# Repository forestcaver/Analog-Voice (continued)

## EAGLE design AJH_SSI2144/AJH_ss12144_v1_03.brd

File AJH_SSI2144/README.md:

# SSI 2144 LPF

Built and tested

CC-BY-NC-SA 4.0

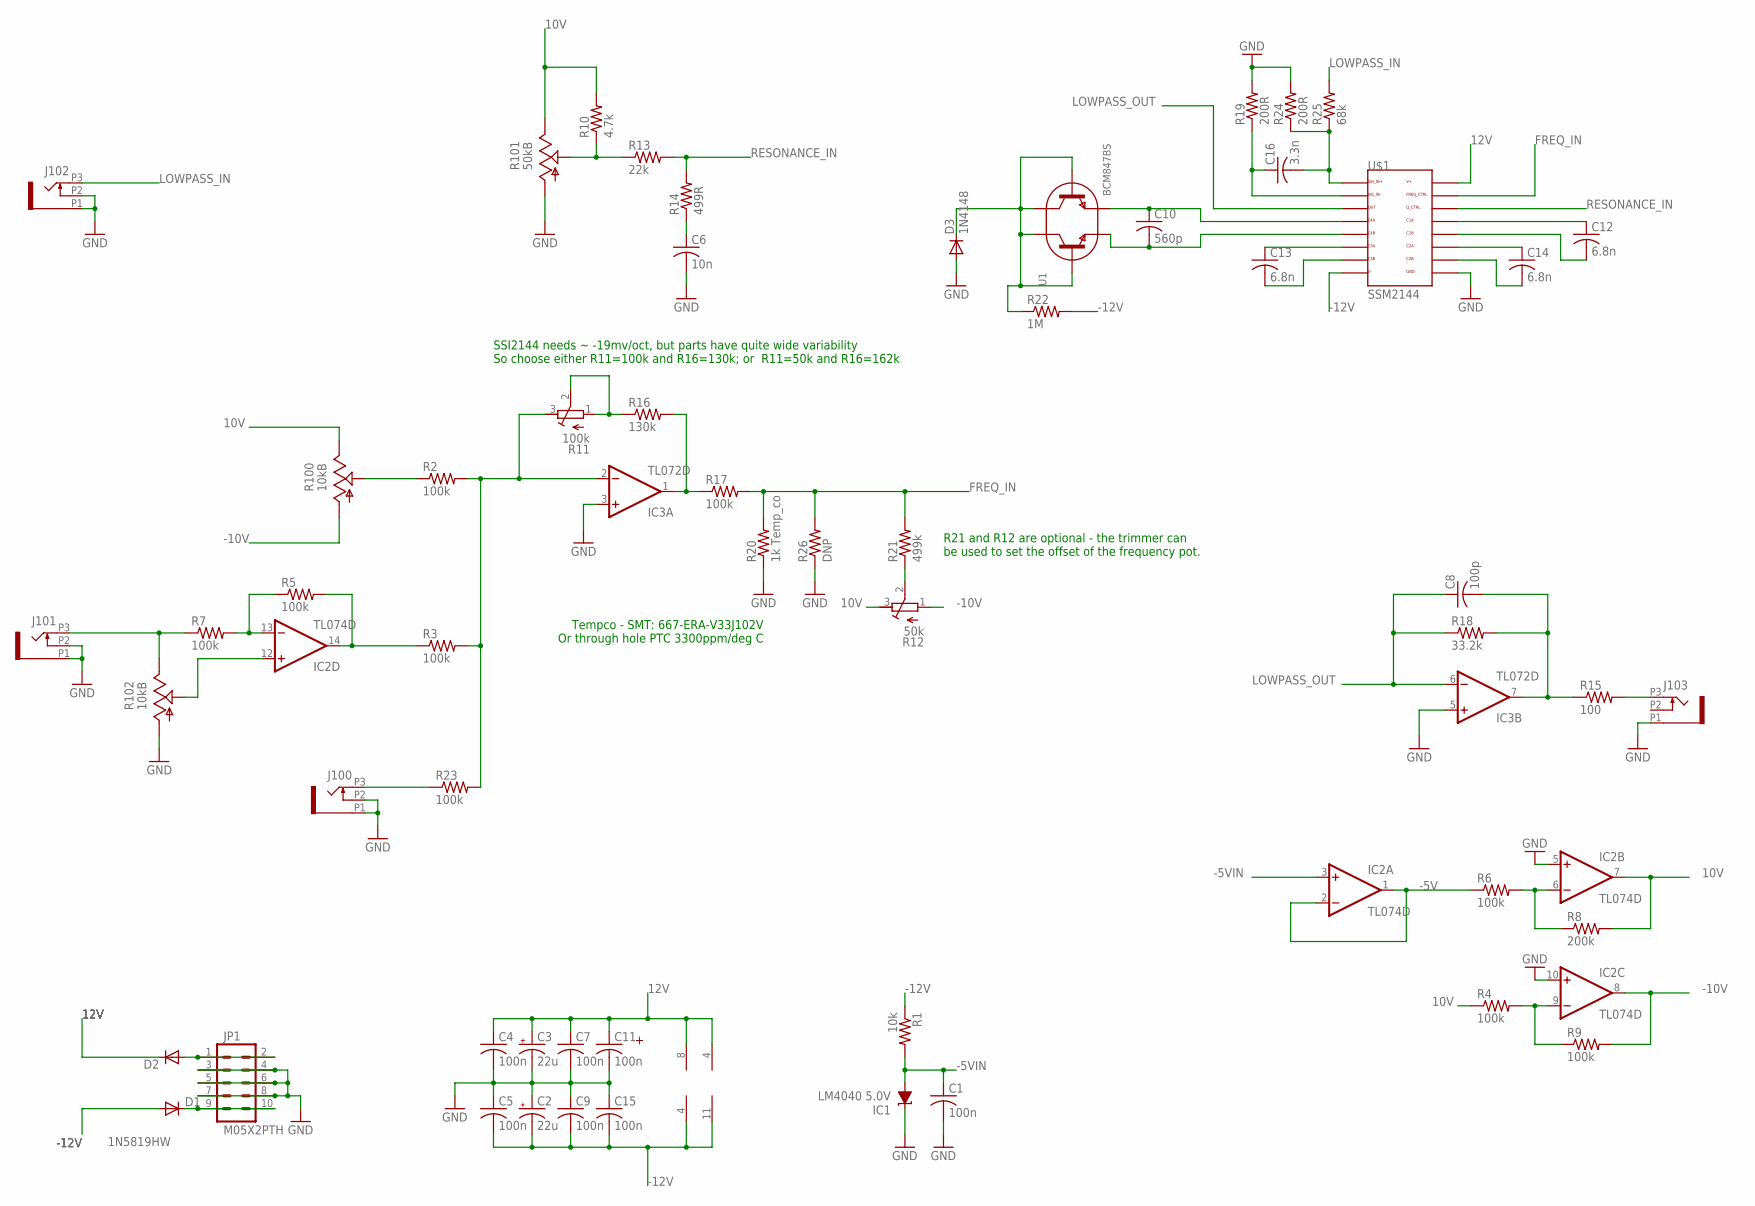
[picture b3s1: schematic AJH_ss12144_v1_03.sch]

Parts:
C1, C4, C5, C7, C9, C11, C15: 100n; C0603
C2, C3: 22u; PANASONIC_B
C6: 10n; C0603
C8: 100p; C0603
C10: 560p; C0603
C12, C13, C14: 6.8n; C0603
C16: 3.3n; C0603
D1, D2: 1N5819HW; SOD123
D3: 1N4148; SOD523
IC1: LM4040 5.0V; DBZ_R-PDSO-G3
IC2: TL074D; SO14
IC3: TL072D; SO08
J100, J101, J102, J103: PJ301_THONKICONN6; WQP_PJ_301M6
JP1: M05X2PTH; AVR_ICSP
R1: 10k; R0603
R2, R3, R4, R5, R6, R7, R9, R17, R23: 100k; R0603
R8: 200k; R0603
R10: 4.7k; R0603
R11: 100k; RTRIM3296X
R12: 50k; RTRIM3296X
R13: 22k; R0603
R14: 499R; R0603
R15: 100; R0603
R16: 130k; R0603
R18: 33.2k; R0603
R19, R24: 200R; R0603
R20: 1k Temp_co; R0603
R21: 499k; R0603
R22: 1M; R0603
R25: 68k; R0603
R26: DNP; 0204/7
R100, R102: 10kB; ALPS_POT_VERTICAL
R101: 50kB; ALPS_POT_VERTICAL
U1: BCM847BS; SOT363
U$1: SSM2144; SSOP16

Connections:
10V: IC2.7 (OUT), R4.1, R8.2, R10.2, R12.3 (A), R100.P$1 (E), R101.P$1 (E)
12V: C3.+, C4.1, C7.1, C11.1, D2.C, IC2.4 (V+), IC3.8 (V+), U$1.16 (V+)
-5V: IC2.1 (OUT), IC2.2 (-IN), R6.1
-5VIN: C1.1, IC1.2 (A), IC2.3 (+IN), R1.2
-10V: IC2.8 (OUT), R9.2, R12.1 (E), R100.P$3 (A)
-12V: C2.-, C5.2, C9.2, C15.2, D1.A, IC2.11 (V-), IC3.4 (V-), R1.1, R22.2, U$1.8 (V-)
FREQ_IN: R17.2, R20.2, R21.2, R26.2, U$1.15 (FREQ_CTRL)
GND: C1.2, C2.+, C3.-, C4.2, C5.1, C6.2, C7.2, C9.1, C11.2, C15.1, D3.A, IC1.1 (C), IC2.5 (+IN), IC2.10 (+IN), IC3.3 (+IN), IC3.5 (+IN), J100.P1 (1), J100.P2 (2), J101.P1 (1), J101.P2 (2), J102.P1 (1), J102.P2 (2), J103.P1 (1), JP1.3, JP1.4, JP1.5, JP1.6, JP1.7, JP1.8, R19.2, R20.1, R24.2, R26.1, R101.P$3 (A), R102.P$3 (A), U$1.9 (GND)
LOWPASS_IN: J102.P3 (3), R25.2
LOWPASS_OUT: C8.1, IC3.6 (-IN), R18.1, U$1.3 (OUT)
unnamed: C8.2, IC3.7 (OUT), R15.1, R18.2
unnamed: C13.1, U$1.6 (C3A)
unnamed: IC2.12 (+IN), R102.P$2 (S)
unnamed: R2.1, R100.P$2 (S)
unnamed: IC2.13 (-IN), R5.1, R7.2
unnamed: D2.A, JP1.1, JP1.2
unnamed: IC3.2 (-IN), R2.2, R3.2, R11.3 (A), R23.2
unnamed: IC3.1 (OUT), R16.2, R17.1
unnamed: C10.1, U1.4 (E2), U$1.4 (C4A)
unnamed: J100.P3 (3), R23.1
unnamed: J103.P3 (3), R15.2
unnamed: IC2.14 (OUT), R3.1, R5.2
unnamed: IC2.9 (-IN), R4.2, R9.1
unnamed: D3.C, R22.1, U1.2 (B1), U1.3 (C2), U1.5 (B2), U1.6 (C1)
unnamed: IC2.6 (-IN), R6.2, R8.1
unnamed: C10.2, U1.1 (E1), U$1.5 (C4B)
unnamed: C13.2, U$1.7 (C3B)
unnamed: C14.2, U$1.10 (C2B)
unnamed: C14.1, U$1.11 (C2A)
unnamed: D1.C, JP1.9, JP1.10
unnamed: C12.1, U$1.13 (C1A)
unnamed: C12.2, U$1.12 (C1B)
unnamed: C16.1, R19.1, U$1.2 (SIG_IN-)
unnamed: R10.1, R13.1, R101.P$2 (S)
unnamed: C6.1, R14.1
unnamed: R12.2 (S), R21.1
unnamed: C16.2, R24.1, R25.1, U$1.1 (SIG_IN+)
unnamed: R11.1 (E), R11.2 (S), R16.1
unnamed: J101.P3 (3), R7.1, R102.P$1 (E)
RESONANCE_IN: R13.2, R14.2, U$1.14 (Q_CTRL)

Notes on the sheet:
Tempco - SMT: 667-ERA-V33J102V Or through hole PTC 3300ppm/deg C
SSI2144 needs ~ -19mv/oct, but parts have quite wide variability So choose either R11=100k and R16=130k; or R11=50k and R16=162k
R21 and R12 are optional - the trimmer can be used to set the offset of the frequency pot.

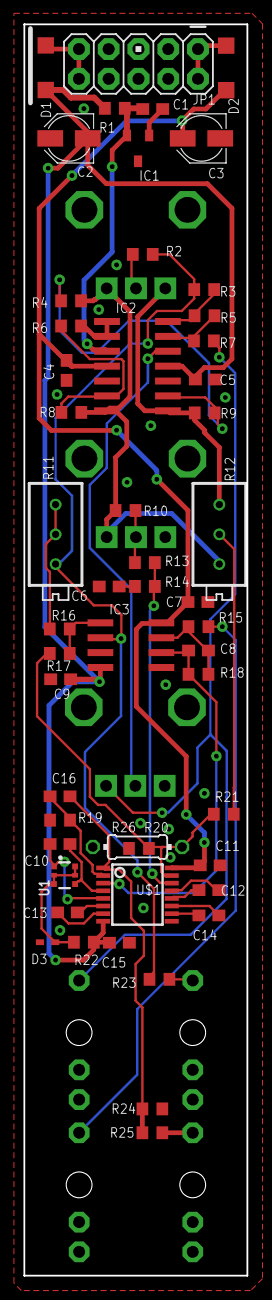
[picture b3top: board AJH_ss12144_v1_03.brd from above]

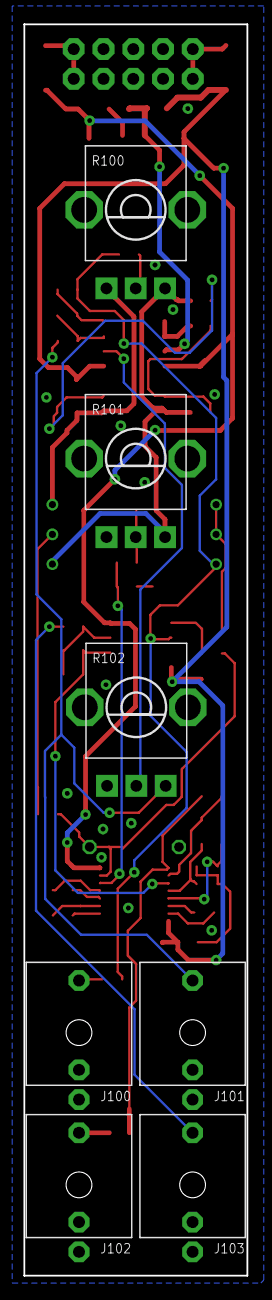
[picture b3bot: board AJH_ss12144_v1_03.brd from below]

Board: 2 copper layers, 19.0 x 106.8 mm, 58 parts (7 on the bottom side), 40 nets.

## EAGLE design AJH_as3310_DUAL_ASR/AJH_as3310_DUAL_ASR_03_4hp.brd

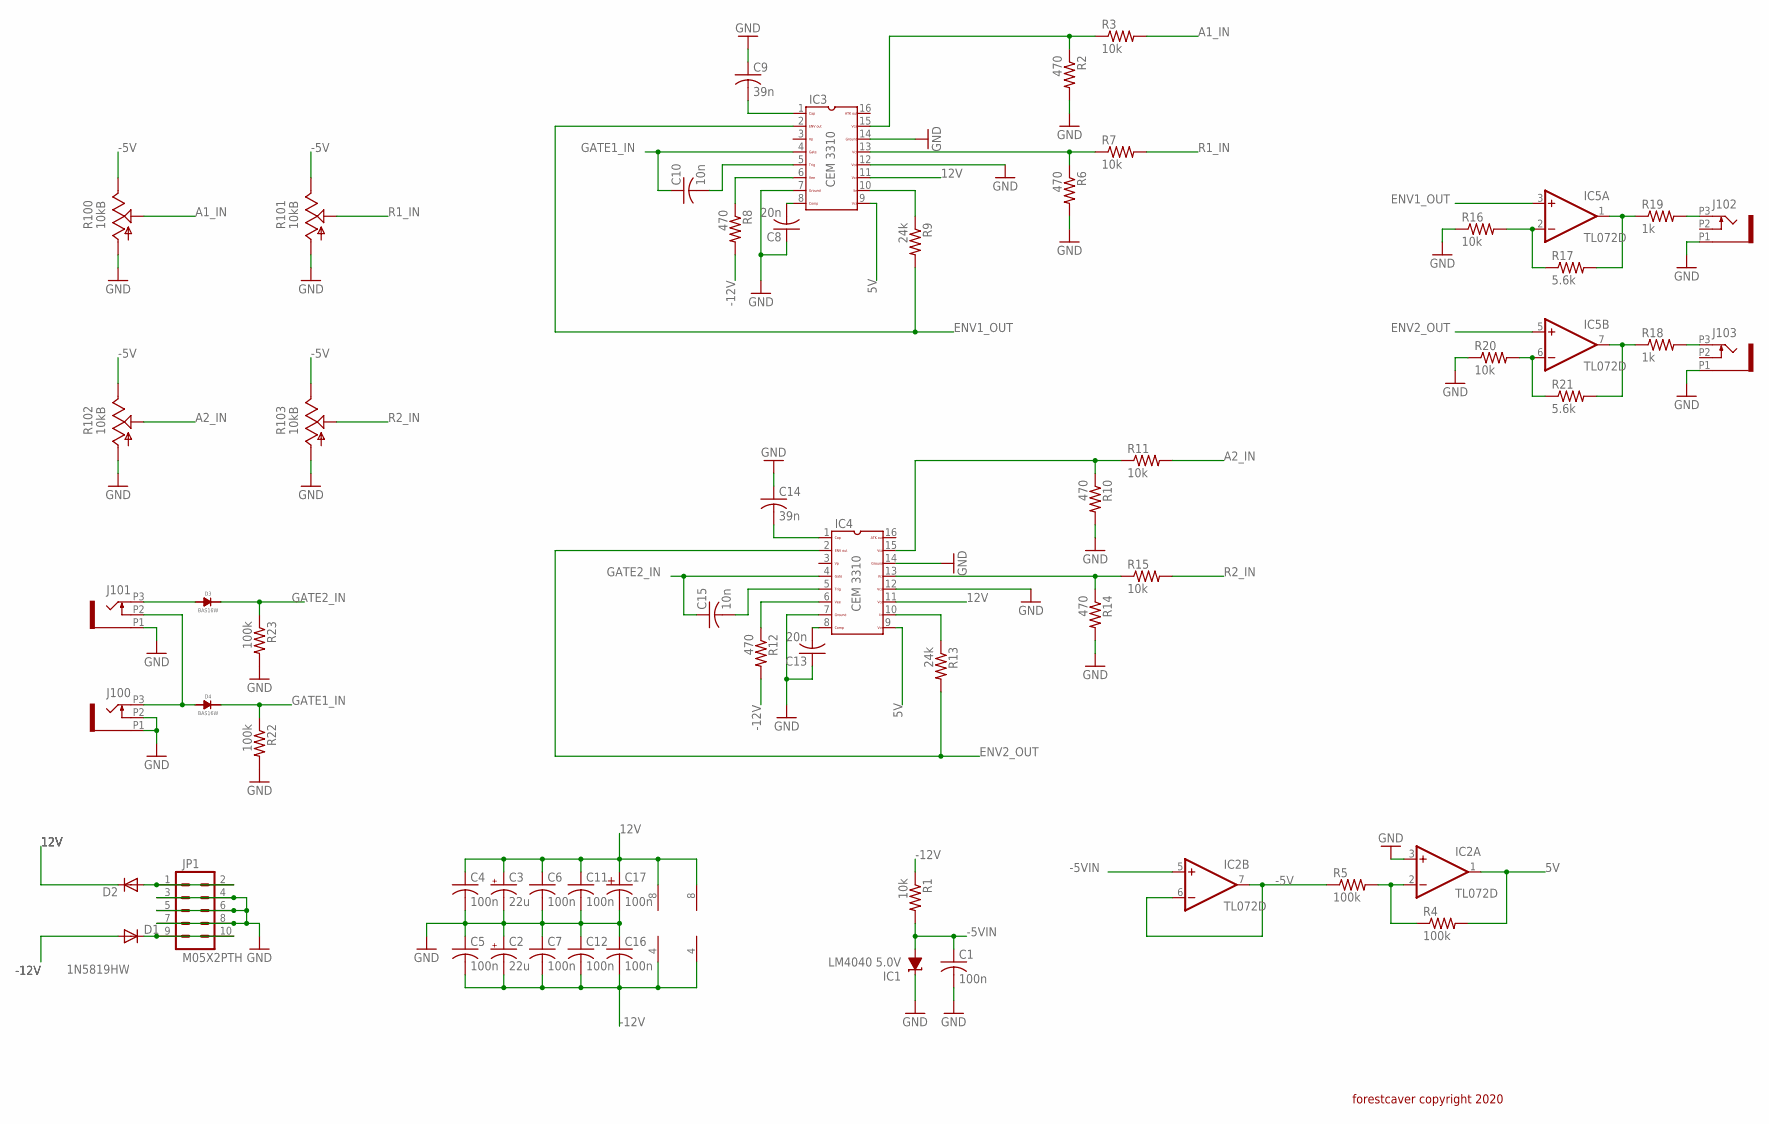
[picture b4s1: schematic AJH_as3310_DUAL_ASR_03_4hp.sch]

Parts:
C1, C4, C5, C6, C7, C11, C12, C16, C17: 100n; C0603
C2, C3: 22u; PANASONIC_B
C8, C13: 20n; C0603
C9, C14: 39n; C0603
C10, C15: 10n; C0603
D1, D2: 1N5819HW; SOD123
D3, D4: BAS16W; SOT-323
IC1: LM4040 5.0V; DBZ_R-PDSO-G3
IC2, IC5: TL072D; SO08
IC3, IC4: CEM3310SOIC16; SO16
J100, J101, J102, J103: PJ301_THONKICONN6; WQP_PJ_301M6
JP1: M05X2PTH; AVR_ICSP
R1, R3, R7, R11, R15, R16, R20: 10k; R0603
R2, R6, R8, R10, R12, R14: 470; R0603
R4, R5, R22, R23: 100k; R0603
R9, R13: 24k; R0603
R17, R21: 5.6k; R0603
R18, R19: 1k; R0603
R100, R101, R102, R103: 10kB; ALPS_POT_VERTICAL

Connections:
5V: IC2.1 (OUT), IC3.9, IC4.9, R4.2
12V: C3.+, C4.1, C6.1, C11.1, C17.1, D2.C, IC2.8 (V+), IC3.11, IC4.11, IC5.8 (V+)
-5V: IC2.6 (-IN), IC2.7 (OUT), R5.1, R100.P$1 (E), R101.P$1 (E), R102.P$1 (E), R103.P$1 (E)
-5VIN: C1.1, IC1.2 (A), IC2.5 (+IN), R1.2
-12V: C2.-, C5.2, C7.2, C12.2, C16.2, D1.A, IC2.4 (V-), IC5.4 (V-), R1.1, R8.2, R12.2
A1_IN: R3.2, R100.P$2 (S)
A2_IN: R11.2, R102.P$2 (S)
ENV1_OUT: IC3.2, IC5.3 (+IN), R9.2
ENV2_OUT: IC4.2, IC5.5 (+IN), R13.2
GATE1_IN: C10.1, D4.CATHODE, IC3.4, R22.1
GATE2_IN: C15.1, D3.CATHODE, IC4.4, R23.1
GND: C1.2, C2.+, C3.-, C4.2, C5.1, C6.2, C7.1, C8.1, C9.1, C11.2, C12.1, C13.1, C14.1, C16.1, C17.2, IC1.1 (C), IC2.3 (+IN), IC3.7, IC3.12, IC3.14, IC4.7, IC4.12, IC4.14, J100.P1 (1), J100.P2 (2), J101.P1 (1), J102.P1 (1), J103.P1 (1), JP1.3, JP1.4, JP1.5, JP1.6, JP1.7, JP1.8, R2.2, R6.2, R10.2, R14.2, R16.1, R20.1, R22.2, R23.2, R100.P$3 (A), R101.P$3 (A), R102.P$3 (A), R103.P$3 (A)
unnamed: D3.ANODE, J101.P3 (3)
unnamed: C15.2, IC4.5
unnamed: C9.2, IC3.1
unnamed: C8.2, IC3.8
unnamed: C10.2, IC3.5
unnamed: D2.A, JP1.1, JP1.2
unnamed: IC3.13, R6.1, R7.1
unnamed: IC3.6, R8.1
unnamed: C13.2, IC4.8
unnamed: IC3.10, R9.1
unnamed: IC4.6, R12.1
unnamed: IC3.15, R2.1, R3.1
unnamed: IC2.2 (-IN), R4.1, R5.2
unnamed: C14.2, IC4.1
unnamed: IC4.10, R13.1
unnamed: IC4.13, R14.1, R15.1
unnamed: IC4.15, R10.1, R11.1
unnamed: IC5.6 (-IN), R20.2, R21.1
unnamed: IC5.7 (OUT), R18.1, R21.2
unnamed: D1.C, JP1.9, JP1.10
unnamed: IC5.2 (-IN), R16.2, R17.1
unnamed: IC5.1 (OUT), R17.2, R19.1
unnamed: J102.P3 (3), R19.2
unnamed: J103.P3 (3), R18.2
unnamed: D4.ANODE, J100.P3 (3), J101.P2 (2)
R1_IN: R7.2, R101.P$2 (S)
R2_IN: R15.2, R103.P$2 (S)

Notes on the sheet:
forestcaver copyright 2020

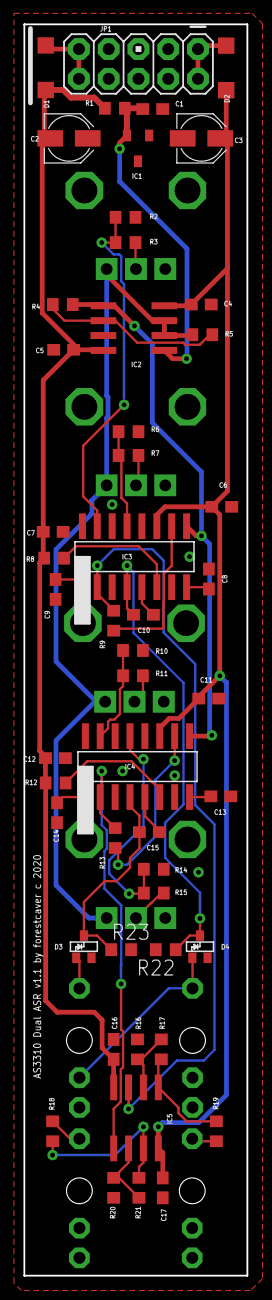
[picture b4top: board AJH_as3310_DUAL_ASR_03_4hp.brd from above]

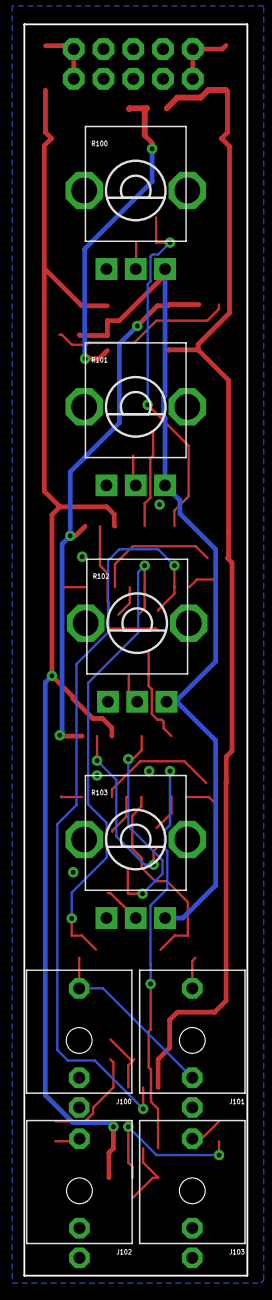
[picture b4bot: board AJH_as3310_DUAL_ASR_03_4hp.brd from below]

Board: 2 copper layers, 19.0 x 106.8 mm, 58 parts (8 on the bottom side), 39 nets.

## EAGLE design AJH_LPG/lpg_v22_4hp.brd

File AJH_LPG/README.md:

# LPG

Built and tested 

CC-BY-NC-SA 4.0

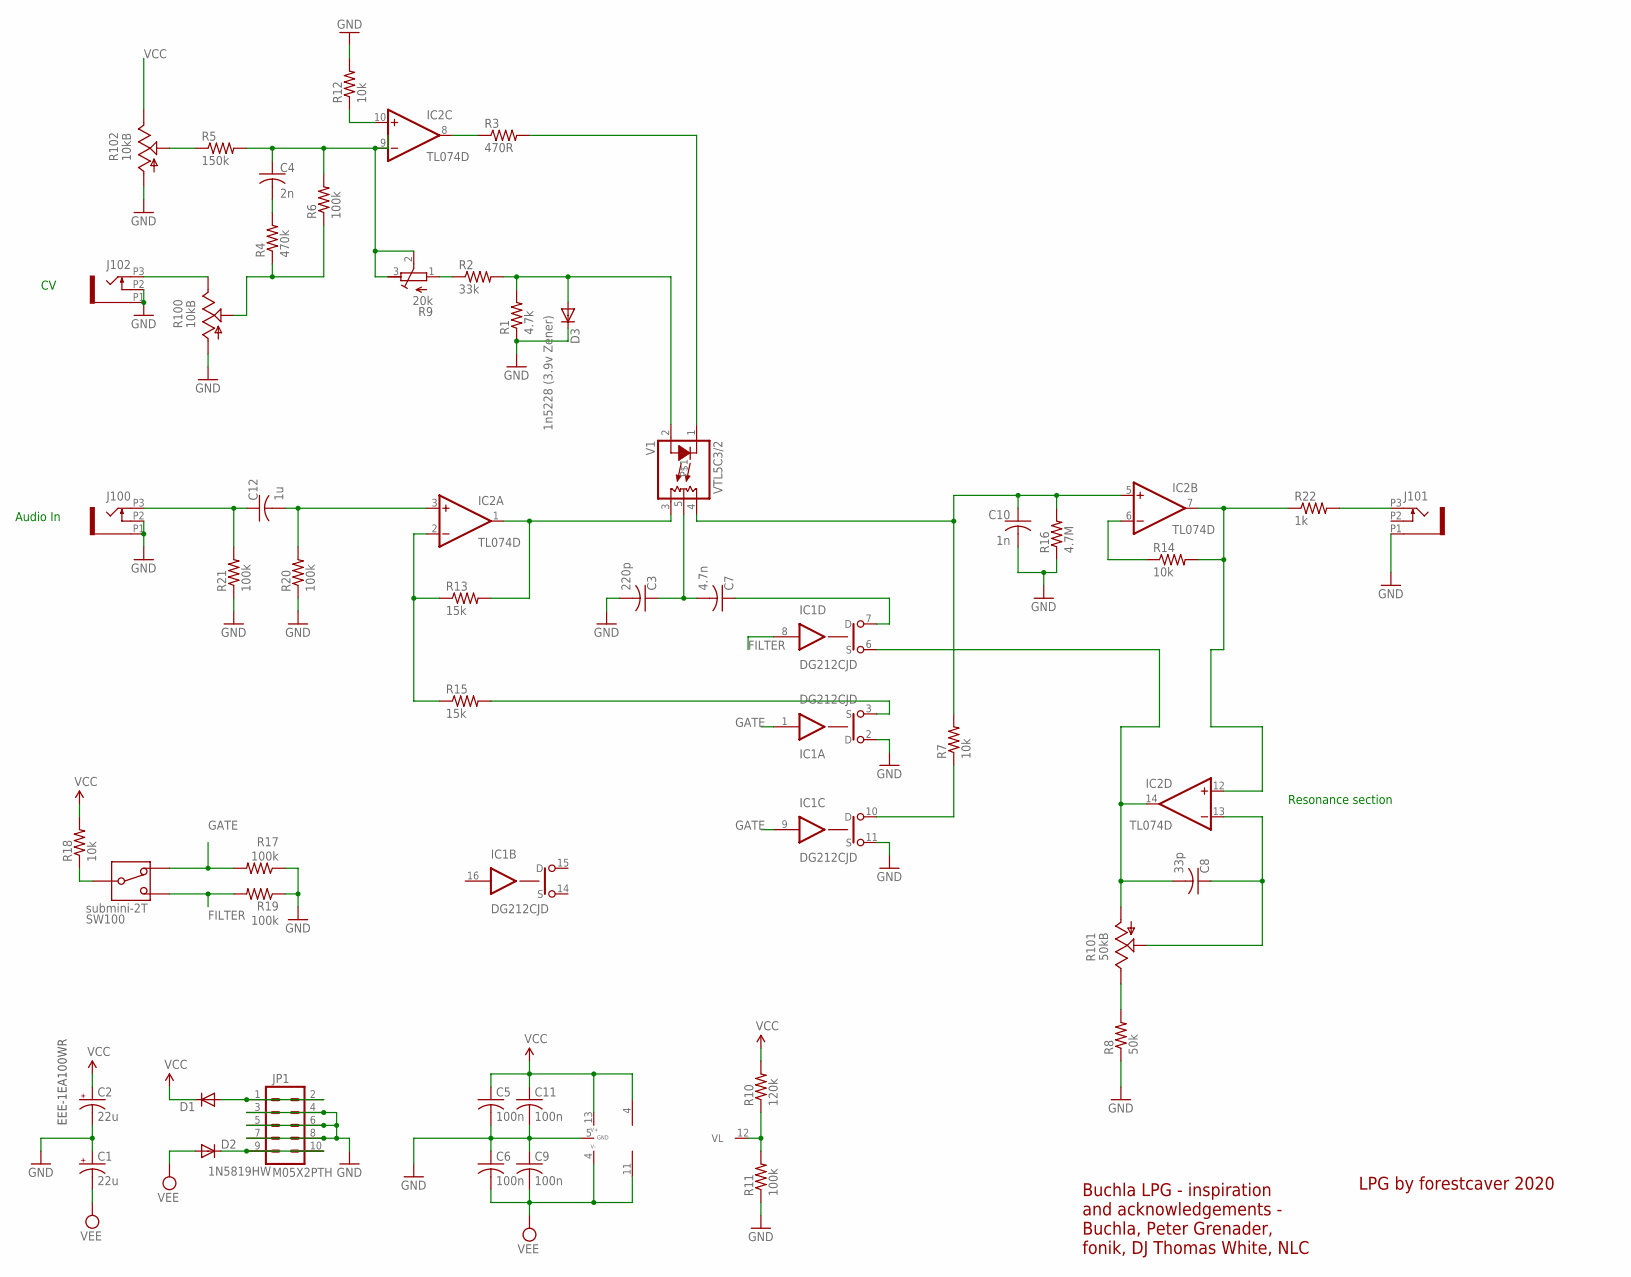
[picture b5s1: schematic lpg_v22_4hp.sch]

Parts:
C1, C2: 22u; PANASONIC_B; MPN EEE-FT1V220AR; MOUSER 667-EEE-FT1V220AR
C3: 220p; C0603
C4: 2n; C0603
C5, C6, C9, C11: 100n; C0603
C7: 4.7n; C0603
C8: 33p; C0603
C10: 1n; C0603
C12: 1u; C0603
D1, D2: 1N5819HW; SOD123
D3: 1n5228 (3.9v Zener); SOD123; MPN MMSZ5228BT1G; MOUSER 863-MMSZ5228BT1G
IC1: DG212CJD; SO16; MPN ADG212AKRZ-REEL; MOUSER 584-ADG212AKRZ-R
IC2: TL074D; SO14; MPN TL074CDR; MOUSER 595-TL074CDR
J100, J101, J102: PJ301_THONKICONN6; WQP_PJ_301M6
JP1: M05X2PTH; AVR_ICSP
R1: 4.7k; R0603
R2: 33k; R0603
R3: 470R; R0603
R4: 470k; R0603
R5: 150k; R0603
R6, R11, R17, R19, R20, R21: 100k; R0603
R7, R12, R14, R18: 10k; R0603
R8: 50k; R0603
R9: 20k; RTRIM3296X
R10: 120k; R0603
R13, R15: 15k; R0603
R16: 4.7M; R0603
R22: 1k; R0603
R100, R102: 10kB; ALPS_POT_VERTICAL_PS
R101: 50kB; ALPS_POT_VERTICAL_PS
SW100: submini-2T; SPDT-SUB
V1: VTL5C3/2; VACTROL_5PIN_VTL5C-2

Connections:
FILTER: IC1.8 (IN), R19.2, SW100.P$1
GATE: IC1.1 (IN), IC1.9 (IN), R17.2, SW100.P$3
GND: C1.+, C2.-, C3.2, C5.2, C6.1, C9.1, C10.2, C11.2, D3.C, IC1.2 (D), IC1.5 (GND), IC1.11 (S), J100.P1 (1), J100.P2 (2), J101.P1 (1), J102.P1 (1), J102.P2 (2), JP1.3, JP1.4, JP1.5, JP1.6, JP1.7, JP1.8, R1.1, R8.1, R11.1, R12.2, R16.1, R17.1, R19.1, R20.1, R21.1, R100.P$3 (A), R102.P$3 (A)
unnamed: IC1.3 (S), R15.2
unnamed: C8.2, IC1.6 (S), IC2.14 (OUT), R101.P$3 (A)
unnamed: IC1.10 (D), R7.1
unnamed: IC1.12 (VL), R10.1, R11.2
unnamed: J102.P3 (3), R100.P$1 (E)
unnamed: D1.A, JP1.1, JP1.2
unnamed: R18.1, SW100.P$2
unnamed: R5.1, R102.P$2 (S)
unnamed: C7.1, IC1.7 (D)
unnamed: C12.2, IC2.3 (+IN), R20.2
unnamed: R8.2, R101.P$1 (E)
unnamed: D2.C, JP1.9, JP1.10
unnamed: C4.2, R4.2
unnamed: R2.1, R9.1 (E)
unnamed: R4.1, R6.1, R100.P$2 (S)
unnamed: IC2.8 (OUT), R3.1
unnamed: IC2.10 (+IN), R12.1
unnamed: C4.1, IC2.9 (-IN), R5.2, R6.2, R9.2 (S), R9.3 (A)
unnamed: D3.A, R1.2, R2.2, V1.2 (A)
unnamed: R3.2, V1.1 (C)
unnamed: C12.1, J100.P3 (3), R21.2
unnamed: IC2.2 (-IN), R13.1, R15.1
unnamed: IC2.1 (OUT), R13.2, V1.3 (L1)
unnamed: C3.1, C7.2, V1.5
unnamed: J101.P3 (3), R22.2
unnamed: IC2.6 (-IN), R14.1
unnamed: IC2.7 (OUT), IC2.12 (+IN), R14.2, R22.1
unnamed: C10.1, IC2.5 (+IN), R7.2, R16.2, V1.4 (L2)
unnamed: C8.1, IC2.13 (-IN), R101.P$2 (S)
VCC: C2.+, C5.1, C11.1, D1.C, IC1.13 (V+), IC2.4 (V+), R10.2, R18.2, R102.P$1 (E)
VEE: C1.-, C6.2, C9.2, D2.A, IC1.4 (V-), IC2.11 (V-)

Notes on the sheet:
EEE-1EA100WR
Audio In
Resonance section
LPG by forestcaver 2020
Buchla LPG - inspiration and acknowledgements - Buchla, Peter Grenader, fonik, DJ Thomas White, NLC

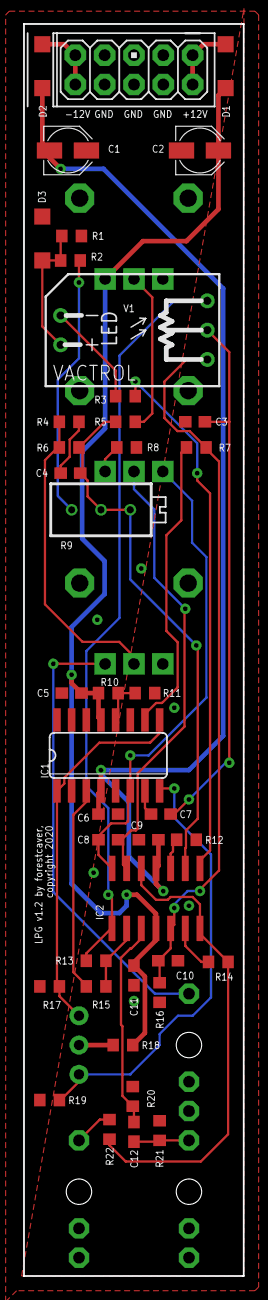
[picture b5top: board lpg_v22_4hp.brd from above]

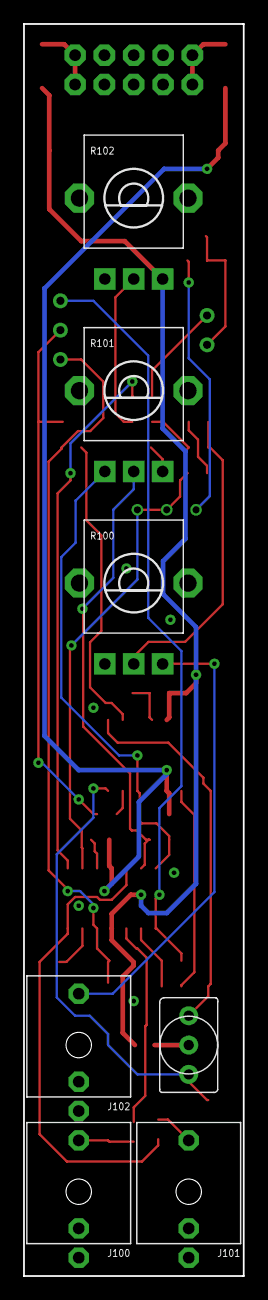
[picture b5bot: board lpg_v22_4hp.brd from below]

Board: 2 copper layers, 19.0 x 108.4 mm, 48 parts (7 on the bottom side), 34 nets.

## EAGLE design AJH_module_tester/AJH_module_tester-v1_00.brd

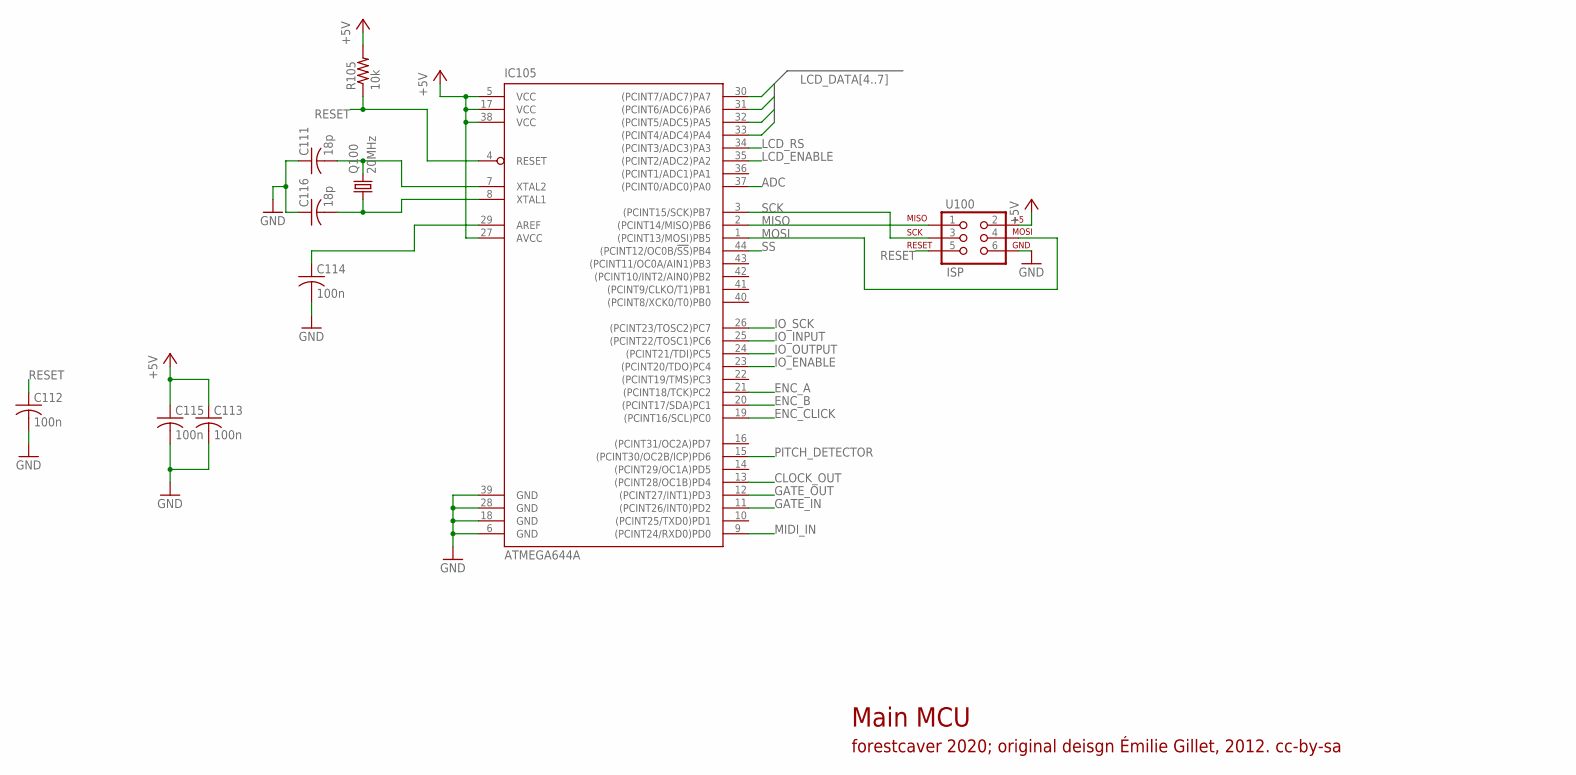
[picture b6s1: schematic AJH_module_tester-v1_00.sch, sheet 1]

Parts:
C111, C116: 18p; C0603
C112, C113, C114, C115: 100n; C0603
IC105: ATMEGA644A; TQFP44
Q100: 20MHz; HC49UP
R105: 10k; R0603
U100: ISP; 2X3

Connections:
+5V: C113.1, C115.1, IC105.5 (VCC), IC105.17 (VCC), IC105.27 (AVCC), IC105.38 (VCC), R105.2, U100.2; also elsewhere on the board
ADC: IC105.37 ((PCINT0/ADC0)PA0); also elsewhere on the board
CLOCK_OUT: IC105.13 ((PCINT28/OC1B)PD4); also elsewhere on the board
ENC_A: IC105.21 ((PCINT18/TCK)PC2); also elsewhere on the board
ENC_B: IC105.20 ((PCINT17/SDA)PC1); also elsewhere on the board
ENC_CLICK: IC105.19 ((PCINT16/SCL)PC0); also elsewhere on the board
GATE_IN: IC105.11 ((PCINT26/INT0)PD2); also elsewhere on the board
GATE_OUT: IC105.12 ((PCINT27/INT1)PD3); also elsewhere on the board
GND: C111.1, C112.2, C113.2, C114.2, C115.2, C116.1, IC105.6 (GND), IC105.18 (GND), IC105.28 (GND), IC105.39 (GND), U100.6; also elsewhere on the board
IO_ENABLE: IC105.23 ((PCINT20/TDO)PC4); also elsewhere on the board
IO_INPUT: IC105.25 ((PCINT22/TOSC1)PC6); also elsewhere on the board
IO_OUTPUT: IC105.24 ((PCINT21/TDI)PC5); also elsewhere on the board
IO_SCK: IC105.26 ((PCINT23/TOSC2)PC7); also elsewhere on the board
LCD_DATA4: IC105.33 ((PCINT4/ADC4)PA4); also elsewhere on the board
LCD_DATA5: IC105.32 ((PCINT5/ADC5)PA5); also elsewhere on the board
LCD_DATA6: IC105.31 ((PCINT6/ADC6)PA6); also elsewhere on the board
LCD_DATA7: IC105.30 ((PCINT7/ADC7)PA7); also elsewhere on the board
LCD_ENABLE: IC105.35 ((PCINT2/ADC2)PA2); also elsewhere on the board
LCD_RS: IC105.34 ((PCINT3/ADC3)PA3); also elsewhere on the board
MIDI_IN: IC105.9 ((PCINT24/RXD0)PD0); also elsewhere on the board
MISO: IC105.2 ((PCINT14/MISO)PB6), U100.1
MOSI: IC105.1 ((PCINT13/MOSI)PB5), U100.4; also elsewhere on the board
unnamed: C116.2, IC105.8 (XTAL1), Q100.1
unnamed: C111.2, IC105.7 (XTAL2), Q100.2
unnamed: C114.1, IC105.29 (AREF)
PITCH_DETECTOR: IC105.15 ((PCINT30/OC2B/ICP)PD6); also elsewhere on the board
RESET: C112.1, IC105.4 (RESET), R105.1, U100.5
SCK: IC105.3 ((PCINT15/SCK)PB7), U100.3; also elsewhere on the board
SS: IC105.44 ((PCINT12/OC0B/!SS!)PB4); also elsewhere on the board

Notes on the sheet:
Main MCU
forestcaver 2020; original deisgn Émilie Gillet, 2012. cc-by-sa

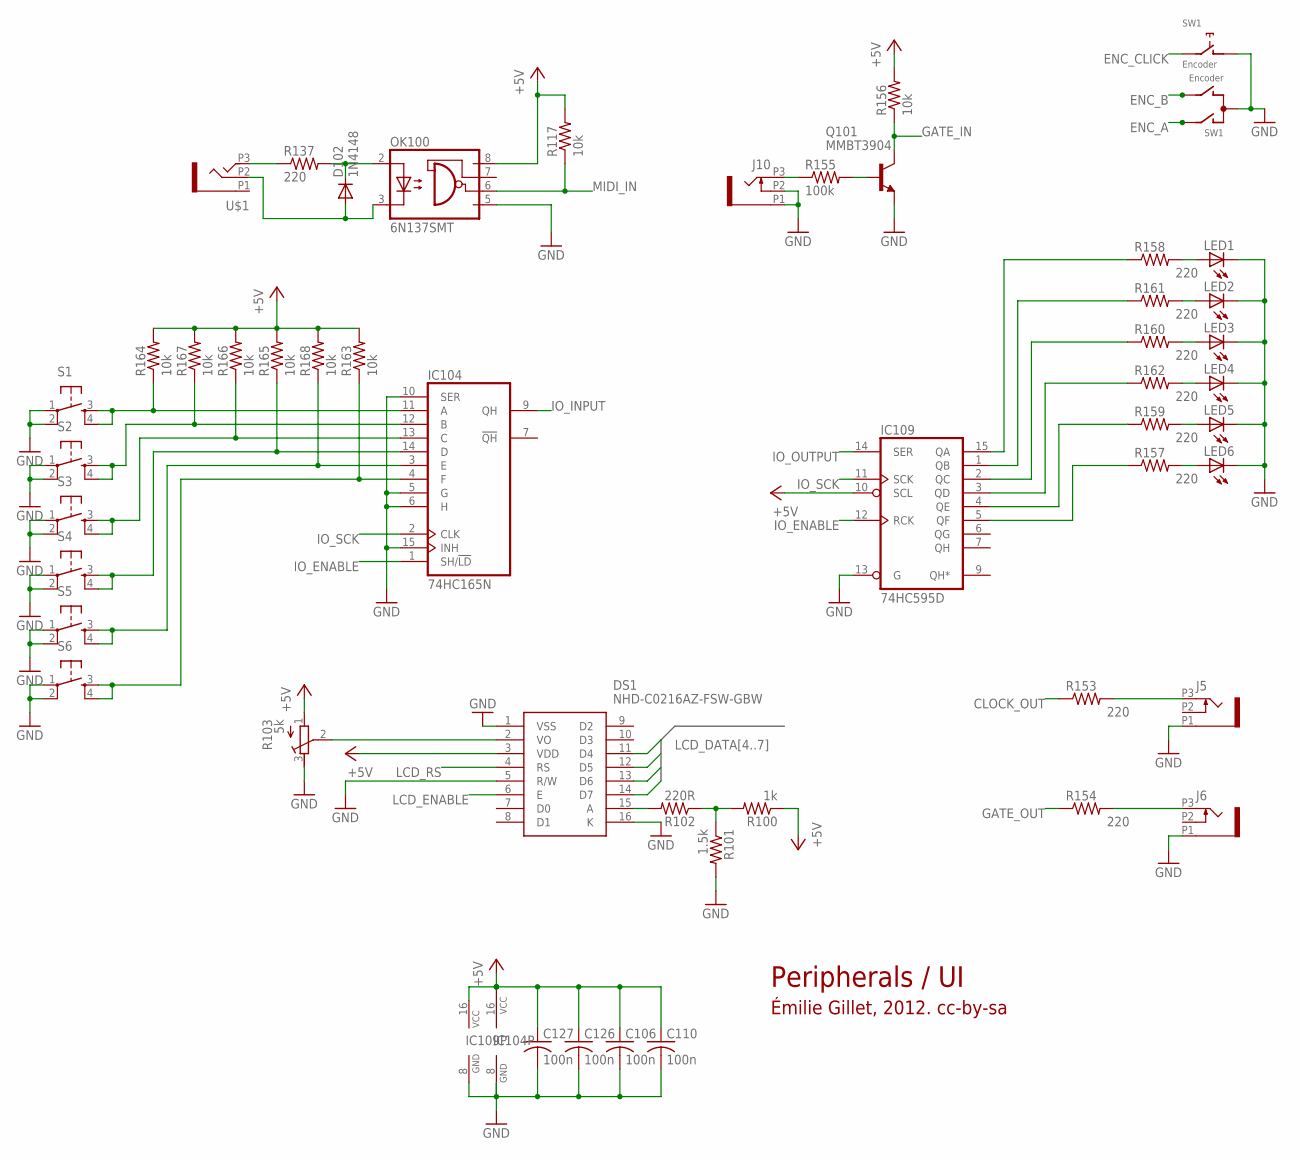
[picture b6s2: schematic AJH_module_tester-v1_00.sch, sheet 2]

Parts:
C106, C110, C126, C127: 100n; C0603
D102: 1N4148; SOD123
DS1: NHD-C0216AZ-FSW-GBW; NHDC0216AZFSWGBW
IC104: 74HC165N; SO16
IC109: 74HC595D; SO16
J5, J6, J10: PJ301_THONKICONN6; WQP_PJ_301M6
LED1, LED2, LED3, LED4, LED5, LED6: LED3MM
OK100: 6N137SMT; DIL8-SMD
Q101: MMBT3904; SOT23-BEC
R100: 1k; R0603
R101: 1.5k; R0603
R102: 220R; R0603
R103: 5k; RTRIM3339P
R117, R156, R163, R164, R165, R166, R167, R168: 10k; R0603
R137, R153, R154, R157, R158, R159, R160, R161, R162: 220; R0603
R155: 100k; R0603
S1, S2, S3, S4, S5, S6: TAC_SWITCHPTH; TACTILE-PTH
SW1: Encoder; ALPS_EC12E_SW
U$1: PJ366ST; WQP_PJ_301M8

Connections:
+5V: C106.1, C110.1, C126.1, C127.1, DS1.3 (VDD), IC104.16 (VCC), IC109.10 (SCL), IC109.16 (VCC), OK100.8 (VCC), R100.1, R103.1 (E), R117.2, R156.2, R163.2, R164.2, R165.2, R166.2, R167.2, R168.2; also elsewhere on the board
CLOCK_OUT: R153.1; also elsewhere on the board
ENC_A: SW1.A; also elsewhere on the board
ENC_B: SW1.B; also elsewhere on the board
ENC_CLICK: SW1.E (2); also elsewhere on the board
GATE_IN: Q101.C, R156.1; also elsewhere on the board
GATE_OUT: R154.1; also elsewhere on the board
GND: C106.2, C110.2, C126.2, C127.2, DS1.1 (VSS), DS1.5 (R/W), DS1.16 (K), IC104.5 (G), IC104.6 (H), IC104.8 (GND), IC104.10 (SER), IC104.15 (INH), IC109.8 (GND), IC109.13 (G), J5.P1 (1), J6.P1 (1), J10.P1 (1), J10.P2 (2), LED1.K (C), LED2.K (C), LED3.K (C), LED4.K (C), LED5.K (C), LED6.K (C), OK100.5 (GND), Q101.E, R101.2, R103.3 (A), S1.1, S1.2, S2.1, S2.2, S3.1, S3.2, S4.1, S4.2, S5.1, S5.2, S6.1, S6.2, SW1.C, SW1.D (1); also elsewhere on the board
IO_ENABLE: IC104.1 (SH/!LD), IC109.12 (RCK); also elsewhere on the board
IO_INPUT: IC104.9 (QH); also elsewhere on the board
IO_OUTPUT: IC109.14 (SER); also elsewhere on the board
IO_SCK: IC104.2 (CLK), IC109.11 (SCK); also elsewhere on the board
LCD_DATA4: DS1.11 (D4); also elsewhere on the board
LCD_DATA5: DS1.12 (D5); also elsewhere on the board
LCD_DATA6: DS1.13 (D6); also elsewhere on the board
LCD_DATA7: DS1.14 (D7); also elsewhere on the board
LCD_ENABLE: DS1.6 (E); also elsewhere on the board
LCD_RS: DS1.4 (RS); also elsewhere on the board
MIDI_IN: OK100.6 (VO), R117.1; also elsewhere on the board
unnamed: IC109.2 (QC), R160.1
unnamed: IC109.4 (QE), R159.1
unnamed: LED5.A, R159.2
unnamed: J10.P3 (3), R155.1
unnamed: R137.1, U$1.P3 (3)
unnamed: IC104.3 (E), R168.1, S5.3, S5.4
unnamed: J5.P3 (3), R153.2
unnamed: IC104.4 (F), R163.1, S6.3, S6.4
unnamed: IC104.14 (D), R165.1, S4.3, S4.4
unnamed: J6.P3 (3), R154.2
unnamed: LED6.A, R157.2
unnamed: IC109.5 (QF), R157.1
unnamed: IC104.11 (A), R164.1, S1.3, S1.4
unnamed: DS1.15 (A), R102.2
unnamed: D102.C, OK100.2 (A), R137.2
unnamed: IC109.15 (QA), R158.1
unnamed: IC109.1 (QB), R161.1
unnamed: IC109.3 (QD), R162.1
unnamed: DS1.2 (VO), R103.2 (S)
unnamed: LED1.A, R158.2
unnamed: LED2.A, R161.2
unnamed: LED3.A, R160.2
unnamed: LED4.A, R162.2
unnamed: R100.2, R101.1, R102.1
unnamed: Q101.B, R155.2
unnamed: D102.A, OK100.3 (C), U$1.P2 (2)
unnamed: IC104.12 (B), R167.1, S2.3, S2.4
unnamed: IC104.13 (C), R166.1, S3.3, S3.4

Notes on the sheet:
Peripherals / UI
Émilie Gillet, 2012. cc-by-sa

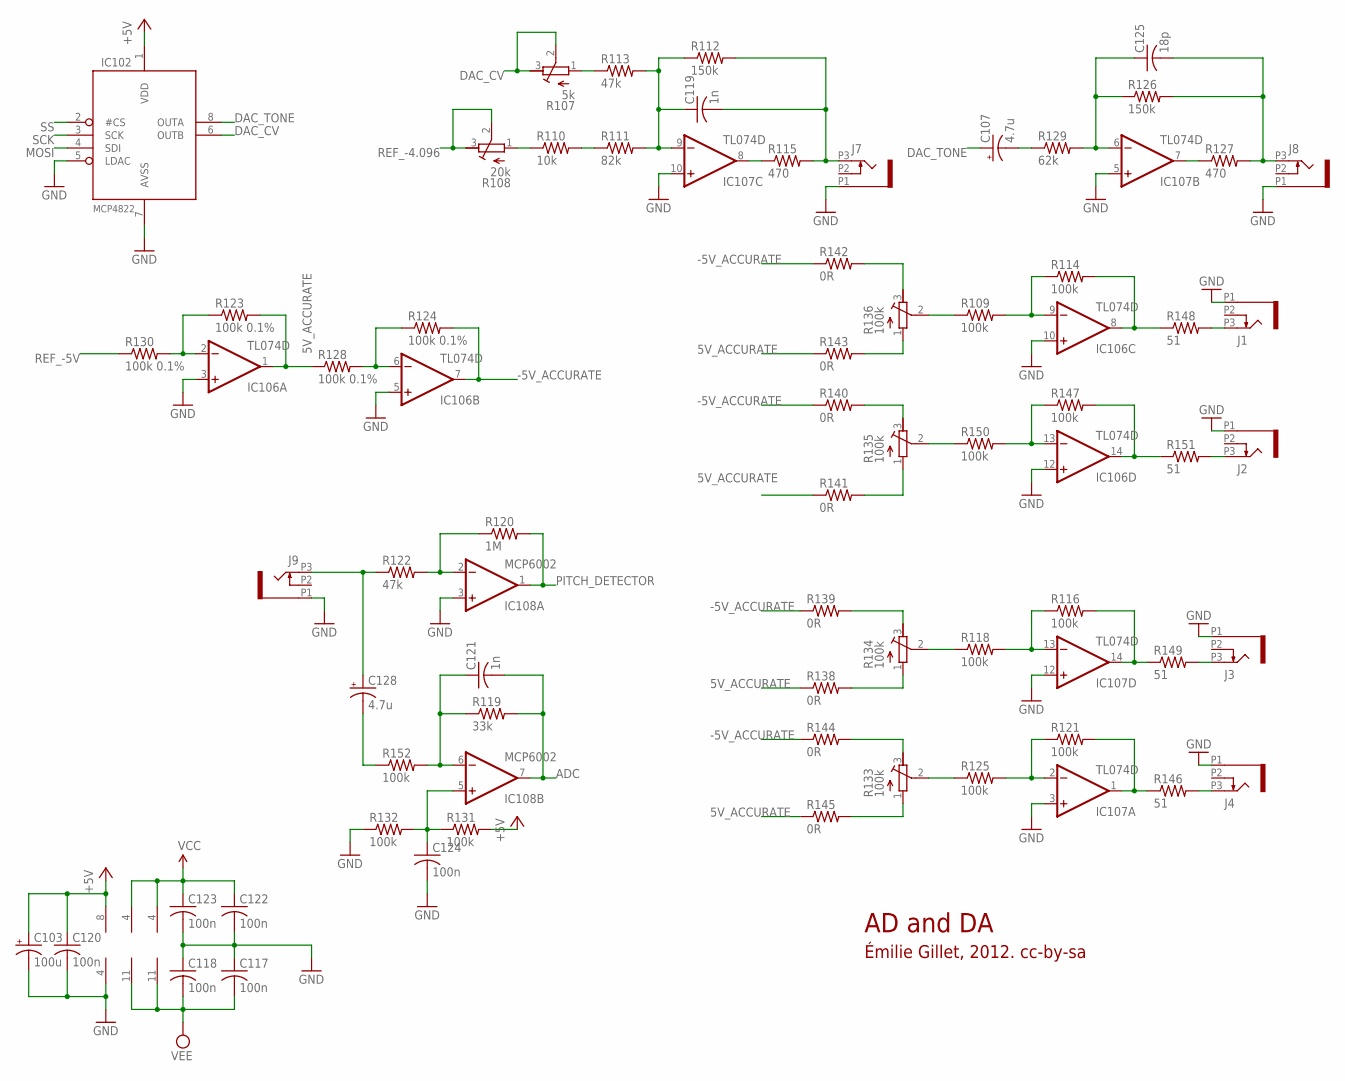
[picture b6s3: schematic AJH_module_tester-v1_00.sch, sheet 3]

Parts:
C103: 100u; PANASONIC_C
C107, C128: 4.7u; PANASONIC_B
C117, C118, C120, C122, C123, C124: 100n; C0603
C119, C121: 1n; C0603
C125: 18p; C0603
IC102: MCP4822SO08; SO08
IC106, IC107: TL074D; SO14
IC108: MCP6002; SO08
J1, J2, J3, J4, J7, J8, J9: PJ301_THONKICONN6; WQP_PJ_301M6
R107: 5k; RTRIM3296W
R108: 20k; RTRIM3296W
R109, R114, R116, R118, R121, R125, R131, R132, R147, R150, R152: 100k; R0603
R110: 10k; R0603
R111: 82k; R0603
R112, R126: 150k; R0603
R113, R122: 47k; R0603
R115, R127: 470; R0603
R119: 33k; R0603
R120: 1M; R0603
R123, R124, R128, R130: 100k 0.1%; R0603
R129: 62k; R0603
R133, R134, R135, R136: 100k; RTRIM3296W
R138, R139, R140, R141, R142, R143, R144, R145: 0R; R0603
R146, R148, R149, R151: 51; R0603

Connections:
5V_ACCURATE: IC106.1 (OUT), R123.2, R128.1, R138.1, R141.1, R143.1, R145.1
+5V: C103.+, C120.1, IC102.1 (VDD), IC108.8 (V+), R131.2; also elsewhere on the board
-5V_ACCURATE: IC106.7 (OUT), R124.2, R139.1, R140.1, R142.1, R144.1
ADC: C121.2, IC108.7 (OUT), R119.2; also elsewhere on the board
DAC_CV: IC102.6 (OUTB), R107.2 (S), R107.3 (A)
DAC_TONE: C107.+, IC102.8 (OUTA)
GND: C103.-, C117.1, C118.1, C120.2, C122.2, C123.2, C124.2, IC102.5 (LDAC), IC102.7 (AVSS), IC106.3 (+IN), IC106.5 (+IN), IC106.10 (+IN), IC106.12 (+IN), IC107.3 (+IN), IC107.5 (+IN), IC107.10 (+IN), IC107.12 (+IN), IC108.3 (+IN), IC108.4 (V-), J1.P1 (1), J2.P1 (1), J3.P1 (1), J4.P1 (1), J7.P1 (1), J8.P1 (1), J9.P1 (1), R132.1; also elsewhere on the board
MOSI: IC102.4 (SDI); also elsewhere on the board
unnamed: C128.+, J9.P3 (3), R122.1
unnamed: IC107.8 (OUT), R115.1
unnamed: IC107.7 (OUT), R127.1
unnamed: IC107.2 (-IN), R121.1, R125.2
unnamed: J2.P3 (3), R151.2
unnamed: C107.-, R129.1
unnamed: J1.P3 (3), R148.2
unnamed: C125.1, IC107.6 (-IN), R126.1, R129.2
unnamed: C119.2, J7.P3 (3), R112.2, R115.2
unnamed: C119.1, IC107.9 (-IN), R111.2, R112.1, R113.2
unnamed: R107.1 (E), R113.1
unnamed: R108.1 (E), R110.1
unnamed: R110.2, R111.1
unnamed: C124.1, IC108.5 (+IN), R131.1, R132.2
unnamed: IC108.2 (-IN), R120.1, R122.2
unnamed: C121.1, IC108.6 (-IN), R119.1, R152.2
unnamed: IC106.14 (OUT), R147.2, R151.1
unnamed: C128.-, R152.1
unnamed: IC107.14 (OUT), R116.2, R149.1
unnamed: IC106.9 (-IN), R109.2, R114.1
unnamed: IC106.8 (OUT), R114.2, R148.1
unnamed: IC106.13 (-IN), R147.1, R150.2
unnamed: IC106.2 (-IN), R123.1, R130.2
unnamed: IC106.6 (-IN), R124.1, R128.2
unnamed: IC107.13 (-IN), R116.1, R118.2
unnamed: R109.1, R136.2 (S)
unnamed: J3.P3 (3), R149.2
unnamed: J4.P3 (3), R146.2
unnamed: IC107.1 (OUT), R121.2, R146.1
unnamed: R135.2 (S), R150.1
unnamed: R125.1, R133.2 (S)
unnamed: R118.1, R134.2 (S)
unnamed: R136.3 (A), R142.2
unnamed: R136.1 (E), R143.2
unnamed: R135.3 (A), R140.2
unnamed: R135.1 (E), R141.2
unnamed: R134.3 (A), R139.2
unnamed: R134.1 (E), R138.2
unnamed: R133.3 (A), R144.2
unnamed: R133.1 (E), R145.2
PITCH_DETECTOR: IC108.1 (OUT), R120.2; also elsewhere on the board
REF_-4.096: R108.2 (S), R108.3 (A); also elsewhere on the board
REF_-5V: R130.1; also elsewhere on the board
SCK: IC102.3 (SCK); also elsewhere on the board
SS: IC102.2 (#CS); also elsewhere on the board
TONE_OUT: C125.2, J8.P3 (3), R126.2, R127.2
VCC: C122.1, C123.1, IC106.4 (V+), IC107.4 (V+); also elsewhere on the board
VEE: C117.2, C118.2, IC106.11 (V-), IC107.11 (V-); also elsewhere on the board

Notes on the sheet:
AD and DA
Émilie Gillet, 2012. cc-by-sa
